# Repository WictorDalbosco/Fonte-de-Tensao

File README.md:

# Fonte-de-Tensao
Projeto da disciplina SSC0180 ([Eletrônica para Computação](https://uspdigital.usp.br/jupiterweb/obterDisciplina?sgldis=SSC0180&codcur=55041&codhab=0)) que visa simular uma fonte de tensão nas especificações recomendadas pelo professor Eduardo Simões

## Especificações: 
A partir da tensão de 127V/220V vinda da tomada, desenvolver uma  fonte que modulariza a corrente alternada (CA) em uma corrente contínua (CC) com saída ajustável de 3V a 12V. Desta forma fornecendo uma capacidade de 100mA.

## Componentes que irão ser utilizados:

|Componente|Especificação|Valor|
|---|---|---|
|Transformador (Trafo)|127 / 24V|[R$24,99](https://produto.mercadolivre.com.br/MLB-1299130767-transformador-1212v-1a-trafo-bivolt-_JM?matt_tool=82322591&matt_word&gclid=EAIaIQobChMI8srS-8u46gIVBg-RCh0u1QKkEAQYASABEgJmHfD_BwE&quantity=1)|
|4 Diodos (Ponte retificadora)|1N4007|[R$0,25](https://www.baudaeletronica.com.br/diodo-1n4007.html)|
|Capacitor Eletrolítico|470 μF 50V|[R$0,33](https://www.baudaeletronica.com.br/capacitor-eletrolitico-470uf-25v.html)|
|Diodo de Zener|1N4743A 13V|[R$0,20](https://www.baudaeletronica.com.br/diodo-zener-1n4743-13v-1w.html)|
|Potenciômetro Rotativo|5kΩ|[R$1,09](https://www.baudaeletronica.com.br/potenciometro-linear-de-5k-5000.html)|
|Transistor NPN|BC337|[R$0,17](https://www.baudaeletronica.com.br/transistor-npn-bc337.html)|
|Resistor|1kΩ|[R$0.08](https://www.baudaeletronica.com.br/resistor-1k-5-1-4w.html)|
|Resistor|4,7kΩ|[R$0,08](https://www.baudaeletronica.com.br/resistor-4k7-5-1-4w.html)|

## Os componentes

- Fonte AC de frequência 60Hz e tensão nominal(VRMS) de 127V, sendo a tensão de pico 127*√2 ≃ 180V;

- Transformador (Trafo) com a VRMS primária de 127V e secundário de 12V, utilizado para a transformação de tensão, reduzindo a amplitude da onda;

- Ponte de diodos completa, composta por 4 diodos, utilizada para retificação (conversão de CA para CC); 

- Capacitor, utilizado para a filtragem (redução de ripple);

- Resistor + diodo zener, o resistor é utilizado para limitar a corrente que chega ao zener, de acordo com a Imax do datasheet. São utilizados para a regulação de tensão;

- Potenciômetro + resistor, o resistor é utilizado para limitar a corrente do ramo caso o potenciômetro esteja com resistência nula. São utilizados para variar a tensão na carga;

- Transistor bipolar NPN, é utilizado para, a partir de uma pequena corrente de base, controlar a corrente que chega a carga.

## Escolha dos Componentes

- Para escolher a fonte, utilizamos a tensão que chega às residências, pois o objetivo do projeto é justamente fazer uma fonte que seja de fácil uso;

- Para escolher o transformador, consideramos que ele aguenta 127V no primário, tendo uma saída no secundário de no mínimo 13V, que pode ser adquirido ao utilizar o tap central do trafo escolhido. Além disso, o transformador deve ser capaz de aguentar a corrente do circuito, que é igual a 100mA;

- Para escolher os diodos, checamos o datasheet:

- Para escolher o capacitor, levamos em consideração os valores padrão disponíveis no mercado e que geram uma redução de ripple aceitável para o projeto;

- Para escolher o diodo zener, checamos o datasheet:

Como a corrente mínima é igual a 19mA e a tensão que chega no circuito é cerca de 18V e a de saída do zener é 13V, deve ter uma queda de 5V no resistor. Colocando um resistor de 470 ohms, facilmente encontrado no mercado, a corrente do zener foi menor que 19mA e atingiu-se o valor final desejado da fonte.

- Para escolher o potenciômetro de 10k e o resistor de 2k, escolhemos valores facilmente encontrados no mercado e que possibilitam atingir o valor desejado na saída da fonte;

- Para escolher o transistor, checamos o datasheet:

## Circuito no Eagle

### Projeto esquemático

### Projeto do PCB

## Slides sobre o projeto
[Ir para os Slides](https://github.com/WictorDalbosco/Fonte-de-Tensao/blob/master/Eletrônica-para-computação.pdf)

## Video do projeto
[Ir para a apresentação do projeto](https://youtu.be/FJlQXyZ5T0k)

## Circuito no falstad

[Simulação do circuito](http://www.falstad.com/circuit/circuitjs.html?cct=$+1+0.000019999999999999998+7.943983955226134+50+5+48%0Av+-96+336+-96+48+0+1+60+127+0+0+0.5%0Aw+96+48+224+48+0%0Ad+224+64+288+128+3+default%0Ad+224+192+288+128+3+default%0Ad+160+128+224+64+3+default%0Ad+160+128+224+192+3+default%0Aw+224+192+224+288+0%0Aw+224+336+96+336+0%0Aw+160+128+160+272+0%0Ac+320+128+320+400+0+0.00047000000000000004+18.326960927829923%0Ar+656+256+656+400+0+120%0Ax+668+305+702+308+4+16+load%0Aw+-96+48+-32+48+0%0Aw+-16+176+-16+48+0%0Aw+-16+48+-32+48+0%0Aw+-16+240+-16+336+0%0Aw+-96+336+-16+336+0%0Aw+64+176+64+48+0%0Aw+64+240+64+336+0%0Aw+64+336+96+336+0%0Aw+64+48+96+48+0%0A34+zvoltage%5Cq12+0+1.7143528192810002e-7+0+2+13%0Az+432+400+432+208+2+zvoltage%5Cq12%0Ag+160+400+160+432+0%0AT+-16+176+64+240+0+4+0.16+-0.21717111847979662+0.00022674181578933488+0.999%0Ar+432+128+432+208+0+1000%0Aw+224+48+224+64+0%0Aw+160+272+160+400+0%0Aw+224+288+224+336+0%0Ar+528+400+528+304+0+4700%0Aw+352+400+320+400+0%0Aw+160+400+320+400+0%0Aw+544+400+528+400+0%0Aw+320+128+288+128+0%0A174+528+304+544+224+1+10000+0.41090000000000004+Resistance%0At+592+240+656+240+0+1+-12.139499694882886+0.6942084449881367+100%0Aw+352+400+432+400+0%0Aw+480+400+528+400+0%0Aw+480+128+528+128+0%0Aw+432+128+480+128+0%0Aw+544+256+592+256+0%0Aw+592+256+592+240+0%0Aw+432+400+480+400+0%0Aw+544+400+560+400+0%0A370+656+400+560+400+1+0%0Ap+720+256+720+400+1+0%0Aw+656+256+720+256+0%0Aw+656+400+720+400+0%0Aw+528+208+432+208+0%0Aw+432+128+320+128+0%0Aw+528+128+656+128+0%0Aw+656+128+656+224+0%0Ax+668+240+745+243+4+16+Transistor%0Ax+504+196+619+199+4+16+Potenci%C3%B4metro%0Ax+375+334+422+337+4+16+Zener%0Ax+239+251+315+254+4+16+Capacitor%0Ax+278+87+424+90+4+16+Ponte%5CsRetificadora%0Ax+44+223+159+226+4+16+Transformador%0Ax+-217+169+-88+172+4+16+Fonte%5Csde%5Cstens%C3%A3o%0Ao+0+8+0+4098+160+0.00009765625+0+2+0+3%0Ao+10+8+0+4099+10+0.05+1+2+10+3%0A)

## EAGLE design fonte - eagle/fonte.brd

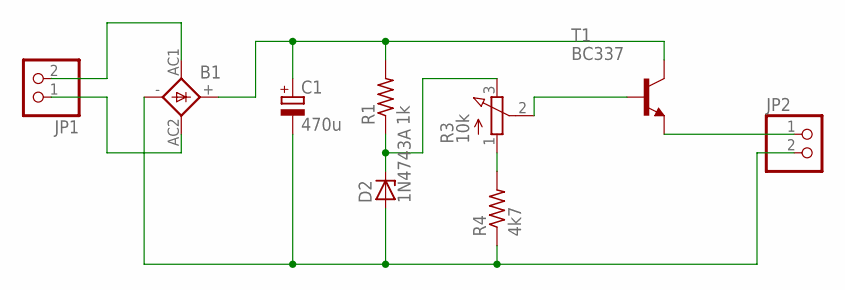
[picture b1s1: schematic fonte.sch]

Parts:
B1: 1KAB
C1: 470u; E3,5-10
D2: 1N4743A; DO41Z10
JP1, JP2: PINHD-1X2; 1X02
R1: 1k; 0309/12
R3: 10k; 3RP/1610N
R4: 4k7; 0309/12
T1: BC337; TO92

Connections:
unnamed: B1.AC1, JP1.2
unnamed: B1.AC2, JP1.1
unnamed: B1.+, C1.+, R1.2, T1.3 (C)
unnamed: B1.-, C1.-, D2.A, JP2.2, R4.1
unnamed: D2.C, R1.1, R3.3 (E)
unnamed: R3.1 (A), R4.2
unnamed: R3.2 (S), T1.2 (B)
unnamed: JP2.1, T1.1 (E)

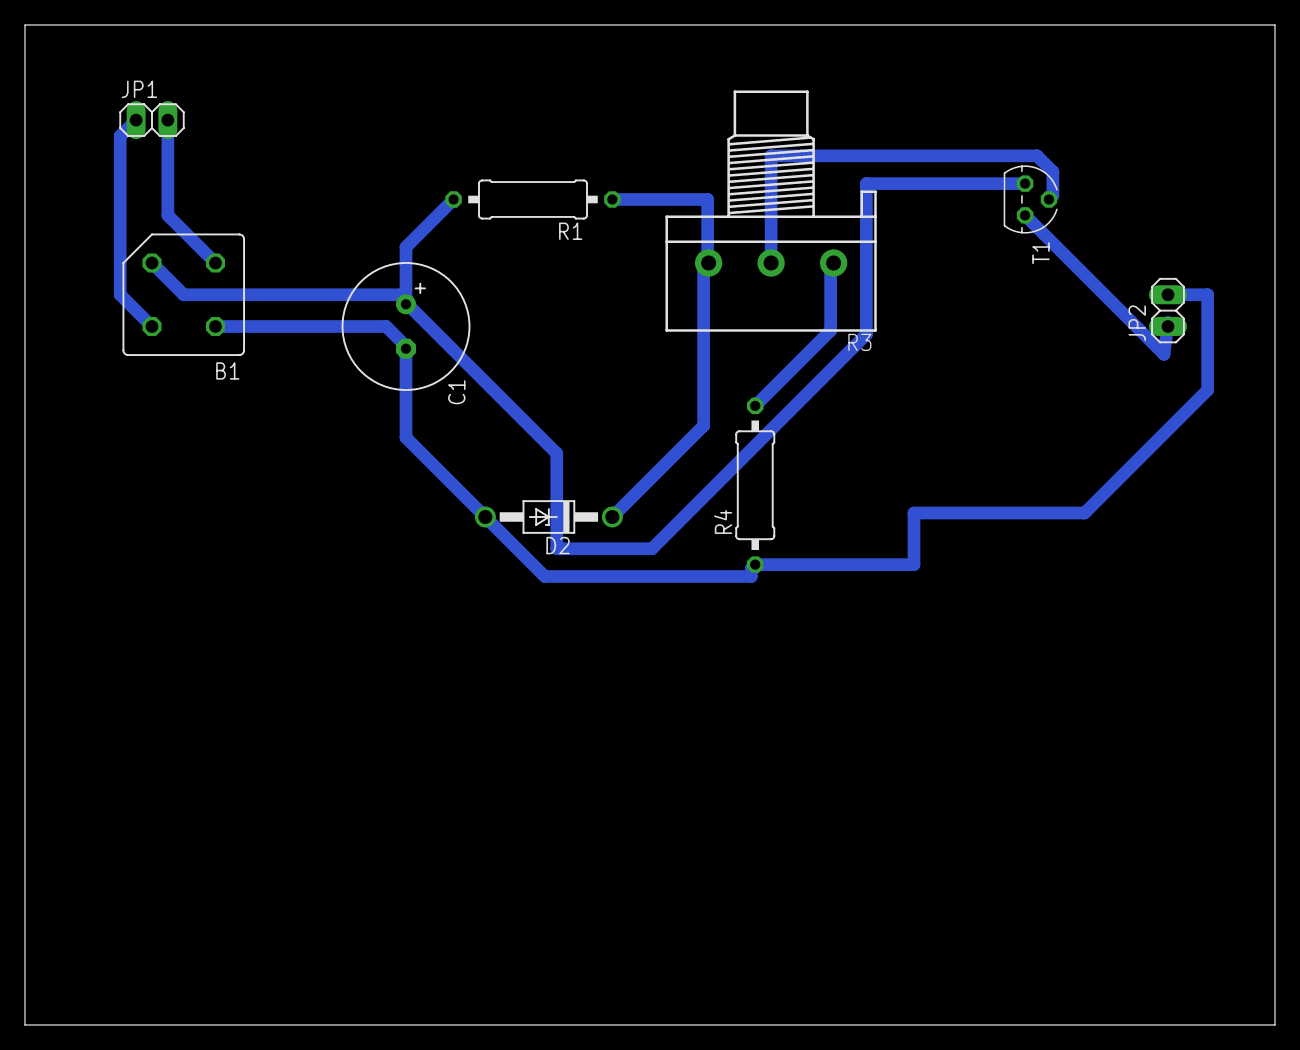
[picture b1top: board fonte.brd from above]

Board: 2 copper layers, 100.0 x 80.0 mm, 9 parts (0 on the bottom side), 8 nets.

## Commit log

2020-07-06 Create Slides
